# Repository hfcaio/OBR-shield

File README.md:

# OBR-shield

This repository share a arduino shield that can be used in rescue line competitions.

## Components

- Arduino Mega (1)
- Sharp sensor (6)
- HC-SR04 (6)
- TCS34725 (4)
- QTR 1a (6)
- servo motor (6)

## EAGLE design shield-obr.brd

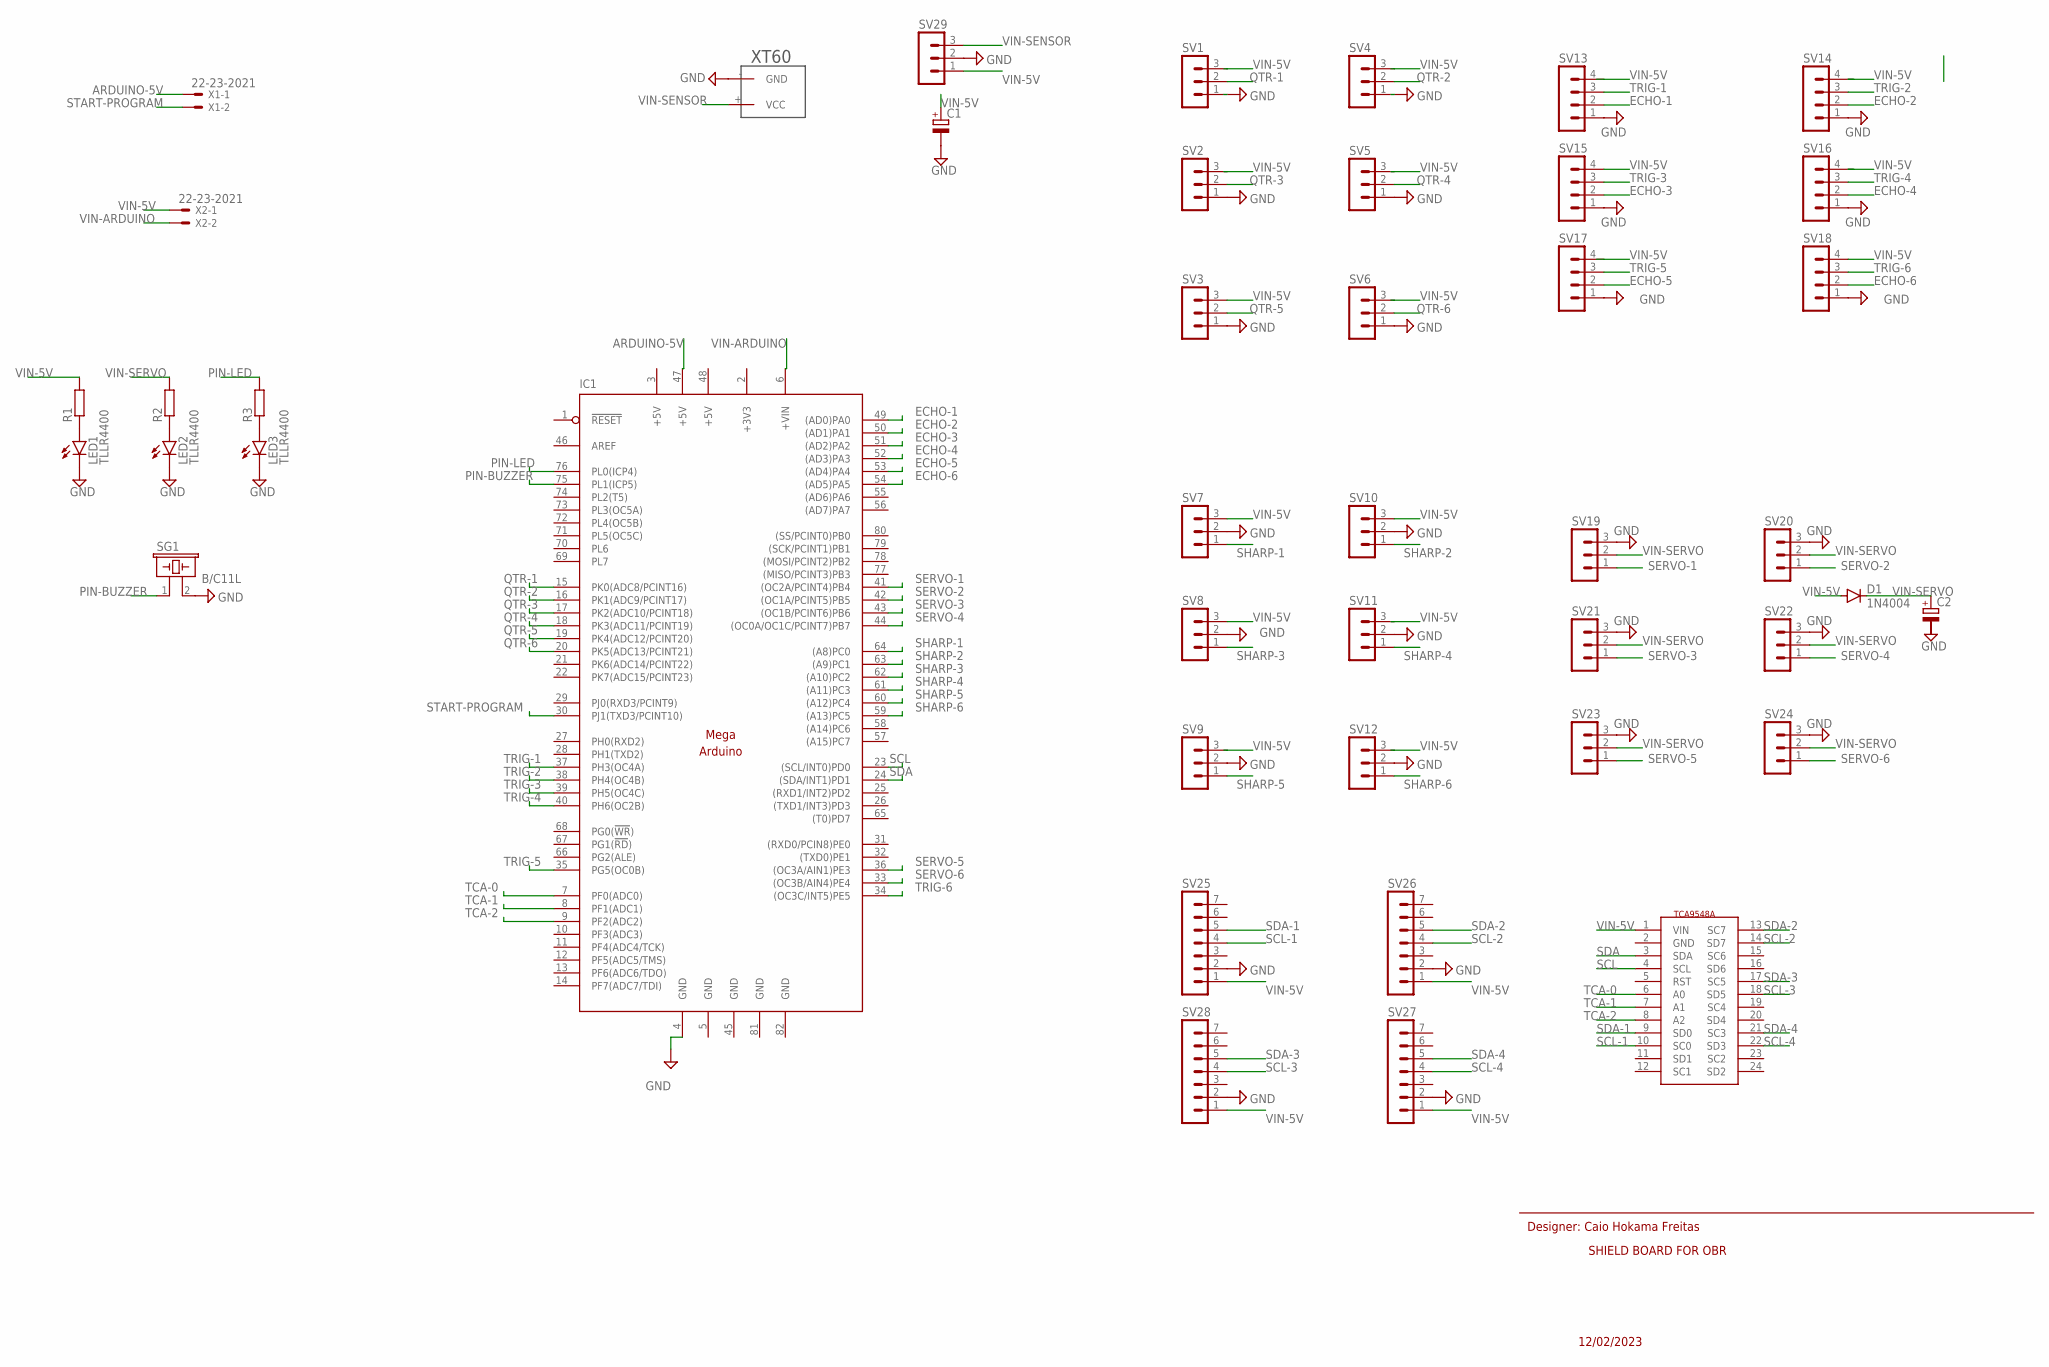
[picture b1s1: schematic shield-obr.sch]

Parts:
C1, C2: CPOL-EUE2.5-5; E2,5-5
D1: 1N4004; DO41-10
IC1: MEGAARDUINO_1; MEGA_ARDUINO
LED1, LED2, LED3: TLLR4400; LED3MM
R1, R2, R3: R-EU_0207/10; 0207/10
SG1: B/C11L
SV1, SV2, SV3, SV4, SV5, SV6, SV7, SV8, SV9, SV10, SV11, SV12, SV19, SV20, SV21, SV22, SV23, SV24, SV29: MA03-1
SV13, SV14, SV15, SV16, SV17, SV18: MA04-1
SV25, SV26, SV27, SV28: MA07-1
U$2: XT60
U$3: TCA9548A
X1, X2: 22-23-2021

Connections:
+3V3: IC1.2 (+3V3)
+5V: IC1.3 (+5V), IC1.48 (+5V)
ARDUINO-5V: IC1.47 (+5V), X1.1
ECHO-1: IC1.49 ((AD0)PA0), SV13.2
ECHO-2: IC1.50 ((AD1)PA1), SV14.2
ECHO-3: IC1.51 ((AD2)PA2), SV15.2
ECHO-4: IC1.52 ((AD3)PA3), SV16.2
ECHO-5: IC1.53 ((AD4)PA4), SV17.2
ECHO-6: IC1.54 ((AD5)PA5), SV18.2
GND: C1.-, IC1.4 (GND), IC1.5 (GND), IC1.45 (GND), IC1.81 (GND), IC1.82 (GND), LED1.K (C), LED2.K (C), LED3.K (C), SG1.2, SV1.1, SV2.1, SV3.1, SV4.1, SV5.1, SV6.1, SV7.2, SV8.2, SV9.2, SV10.2, SV11.2, SV12.2, SV13.1, SV14.1, SV15.1, SV16.1, SV17.1, SV18.1, SV19.3, SV20.3, SV21.3, SV22.3, SV23.3, SV24.3, SV25.2, SV26.2, SV27.2, SV28.2, SV29.2, U$2.- (GND)
unnamed: LED1.A, R1.1
unnamed: LED2.A, R2.1
unnamed: LED3.A, R3.1
PIN-BUZZER: IC1.75 (PL1(ICP5)), SG1.1
PIN-LED: IC1.76 (PL0(ICP4)), R3.2
QTR-1: IC1.15 (PK0(ADC8/PCINT16)), SV1.2
QTR-2: IC1.16 (PK1(ADC9/PCINT17)), SV4.2
QTR-3: IC1.17 (PK2(ADC10/PCINT18)), SV2.2
QTR-4: IC1.18 (PK3(ADC11/PCINT19)), SV5.2
QTR-5: IC1.19 (PK4(ADC12/PCINT20)), SV3.2
QTR-6: IC1.20 (PK5(ADC13/PCINT21)), SV6.2
SCL: IC1.23 ((SCL/INT0)PD0), U$3.4 (SCL)
SCL-1: SV25.4, U$3.10 (SC0)
SCL-2: SV26.4, U$3.14 (SD7)
SCL-3: SV28.4, U$3.18 (SD5)
SCL-4: SV27.4, U$3.22 (SD3)
SDA: IC1.24 ((SDA/INT1)PD1), U$3.3 (SDA)
SDA-1: SV25.5, U$3.9 (SD0)
SDA-2: SV26.5, U$3.13 (SC7)
SDA-3: SV28.5, U$3.17 (SC5)
SDA-4: SV27.5, U$3.21 (SC3)
SERVO-1: IC1.41 ((OC2A/PCINT4)PB4), SV19.1
SERVO-2: IC1.42 ((OC1A/PCINT5)PB5), SV20.1
SERVO-3: IC1.43 ((OC1B/PCINT6)PB6), SV21.1
SERVO-4: IC1.44 ((OC0A/OC1C/PCINT7)PB7), SV22.1
SERVO-5: IC1.36 ((OC3A/AIN1)PE3), SV23.1
SERVO-6: IC1.33 ((OC3B/AIN4)PE4), SV24.1
SHARP-1: IC1.64 ((A8)PC0), SV7.1
SHARP-2: IC1.63 ((A9)PC1), SV10.1
SHARP-3: IC1.62 ((A10)PC2), SV8.1
SHARP-4: IC1.61 ((A11)PC3), SV11.1
SHARP-5: IC1.60 ((A12)PC4), SV9.1
SHARP-6: IC1.59 ((A13)PC5), SV12.1
START-PROGRAM: IC1.30 (PJ1(TXD3/PCINT10)), X1.2
TCA-0: IC1.7 (PF0(ADC0)), U$3.6 (A0)
TCA-1: IC1.8 (PF1(ADC1)), U$3.7 (A1)
TCA-2: IC1.9 (PF2(ADC2)), U$3.8 (A2)
TRIG-1: IC1.37 (PH3(OC4A)), SV13.3
TRIG-2: IC1.38 (PH4(OC4B)), SV14.3
TRIG-3: IC1.39 (PH5(OC4C)), SV15.3
TRIG-4: IC1.40 (PH6(OC2B)), SV16.3
TRIG-5: IC1.35 (PG5(OC0B)), SV17.3
TRIG-6: IC1.34 ((OC3C/INT5)PE5), SV18.3
VIN-5V: C1.+, D1.A, R1.2, SV1.3, SV2.3, SV3.3, SV4.3, SV5.3, SV6.3, SV7.3, SV8.3, SV9.3, SV10.3, SV11.3, SV12.3, SV13.4, SV14.4, SV15.4, SV16.4, SV17.4, SV18.4, SV25.1, SV26.1, SV27.1, SV28.1, SV29.1, U$3.1 (VIN), X2.1
VIN-ARDUINO: IC1.6 (+VIN), X2.2
VIN-SENSOR: SV29.3, U$2.+ (VCC)
VIN-SERVO: C2.+, D1.C, R2.2, SV19.2, SV20.2, SV21.2, SV22.2, SV23.2, SV24.2

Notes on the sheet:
Designer: Caio Hokama Freitas
SHIELD BOARD FOR OBR
12/02/2023

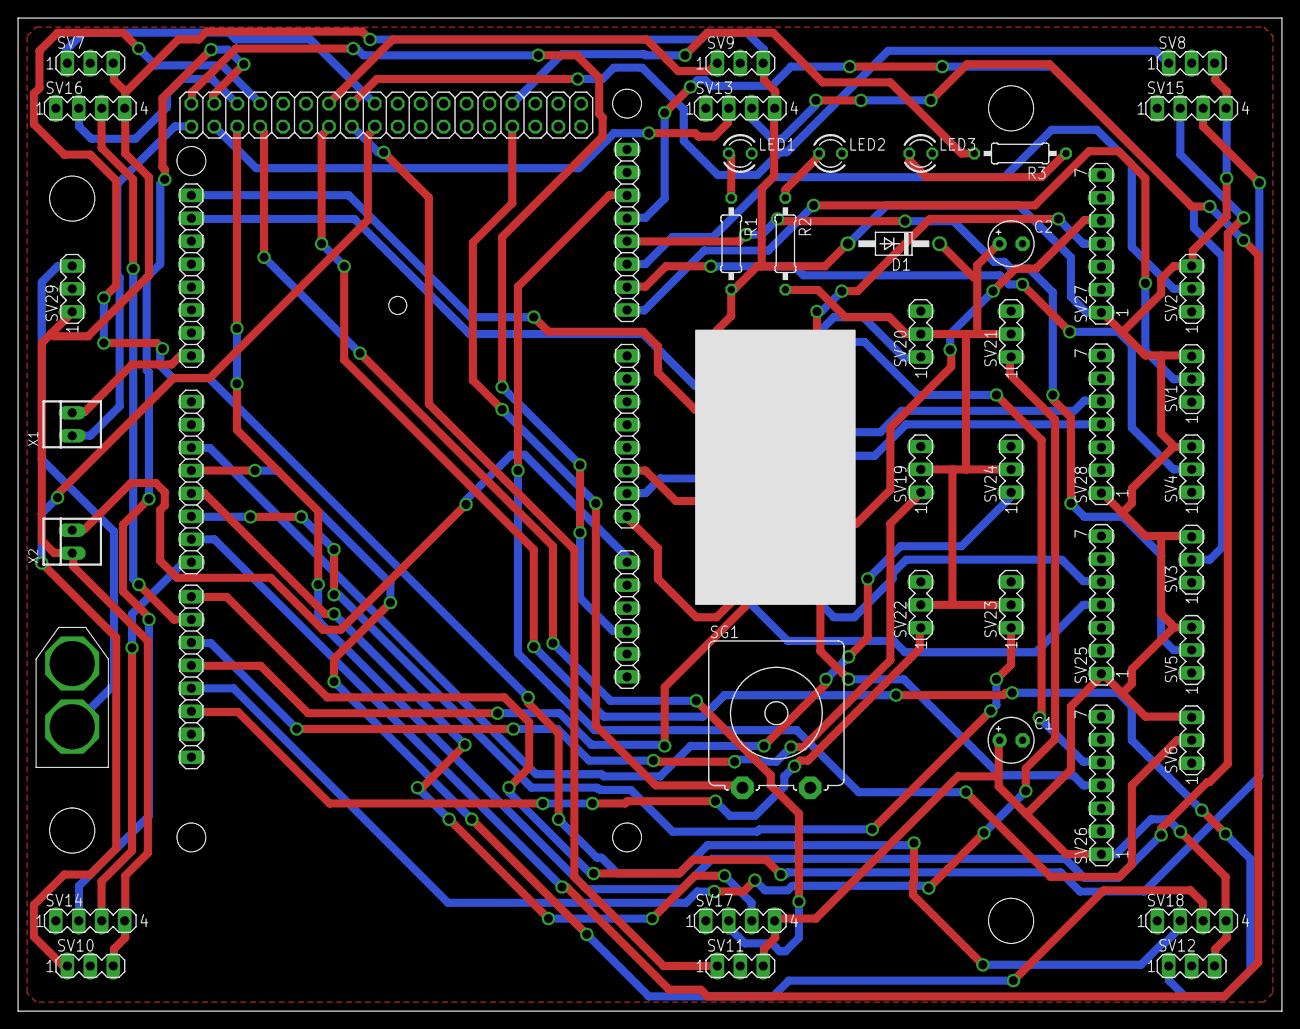
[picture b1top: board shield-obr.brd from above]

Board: 2 copper layers, 140.0 x 110.0 mm, 44 parts (0 on the bottom side), 56 nets.

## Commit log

2023-04-12 create LICENSE
2023-04-12 create a README file
